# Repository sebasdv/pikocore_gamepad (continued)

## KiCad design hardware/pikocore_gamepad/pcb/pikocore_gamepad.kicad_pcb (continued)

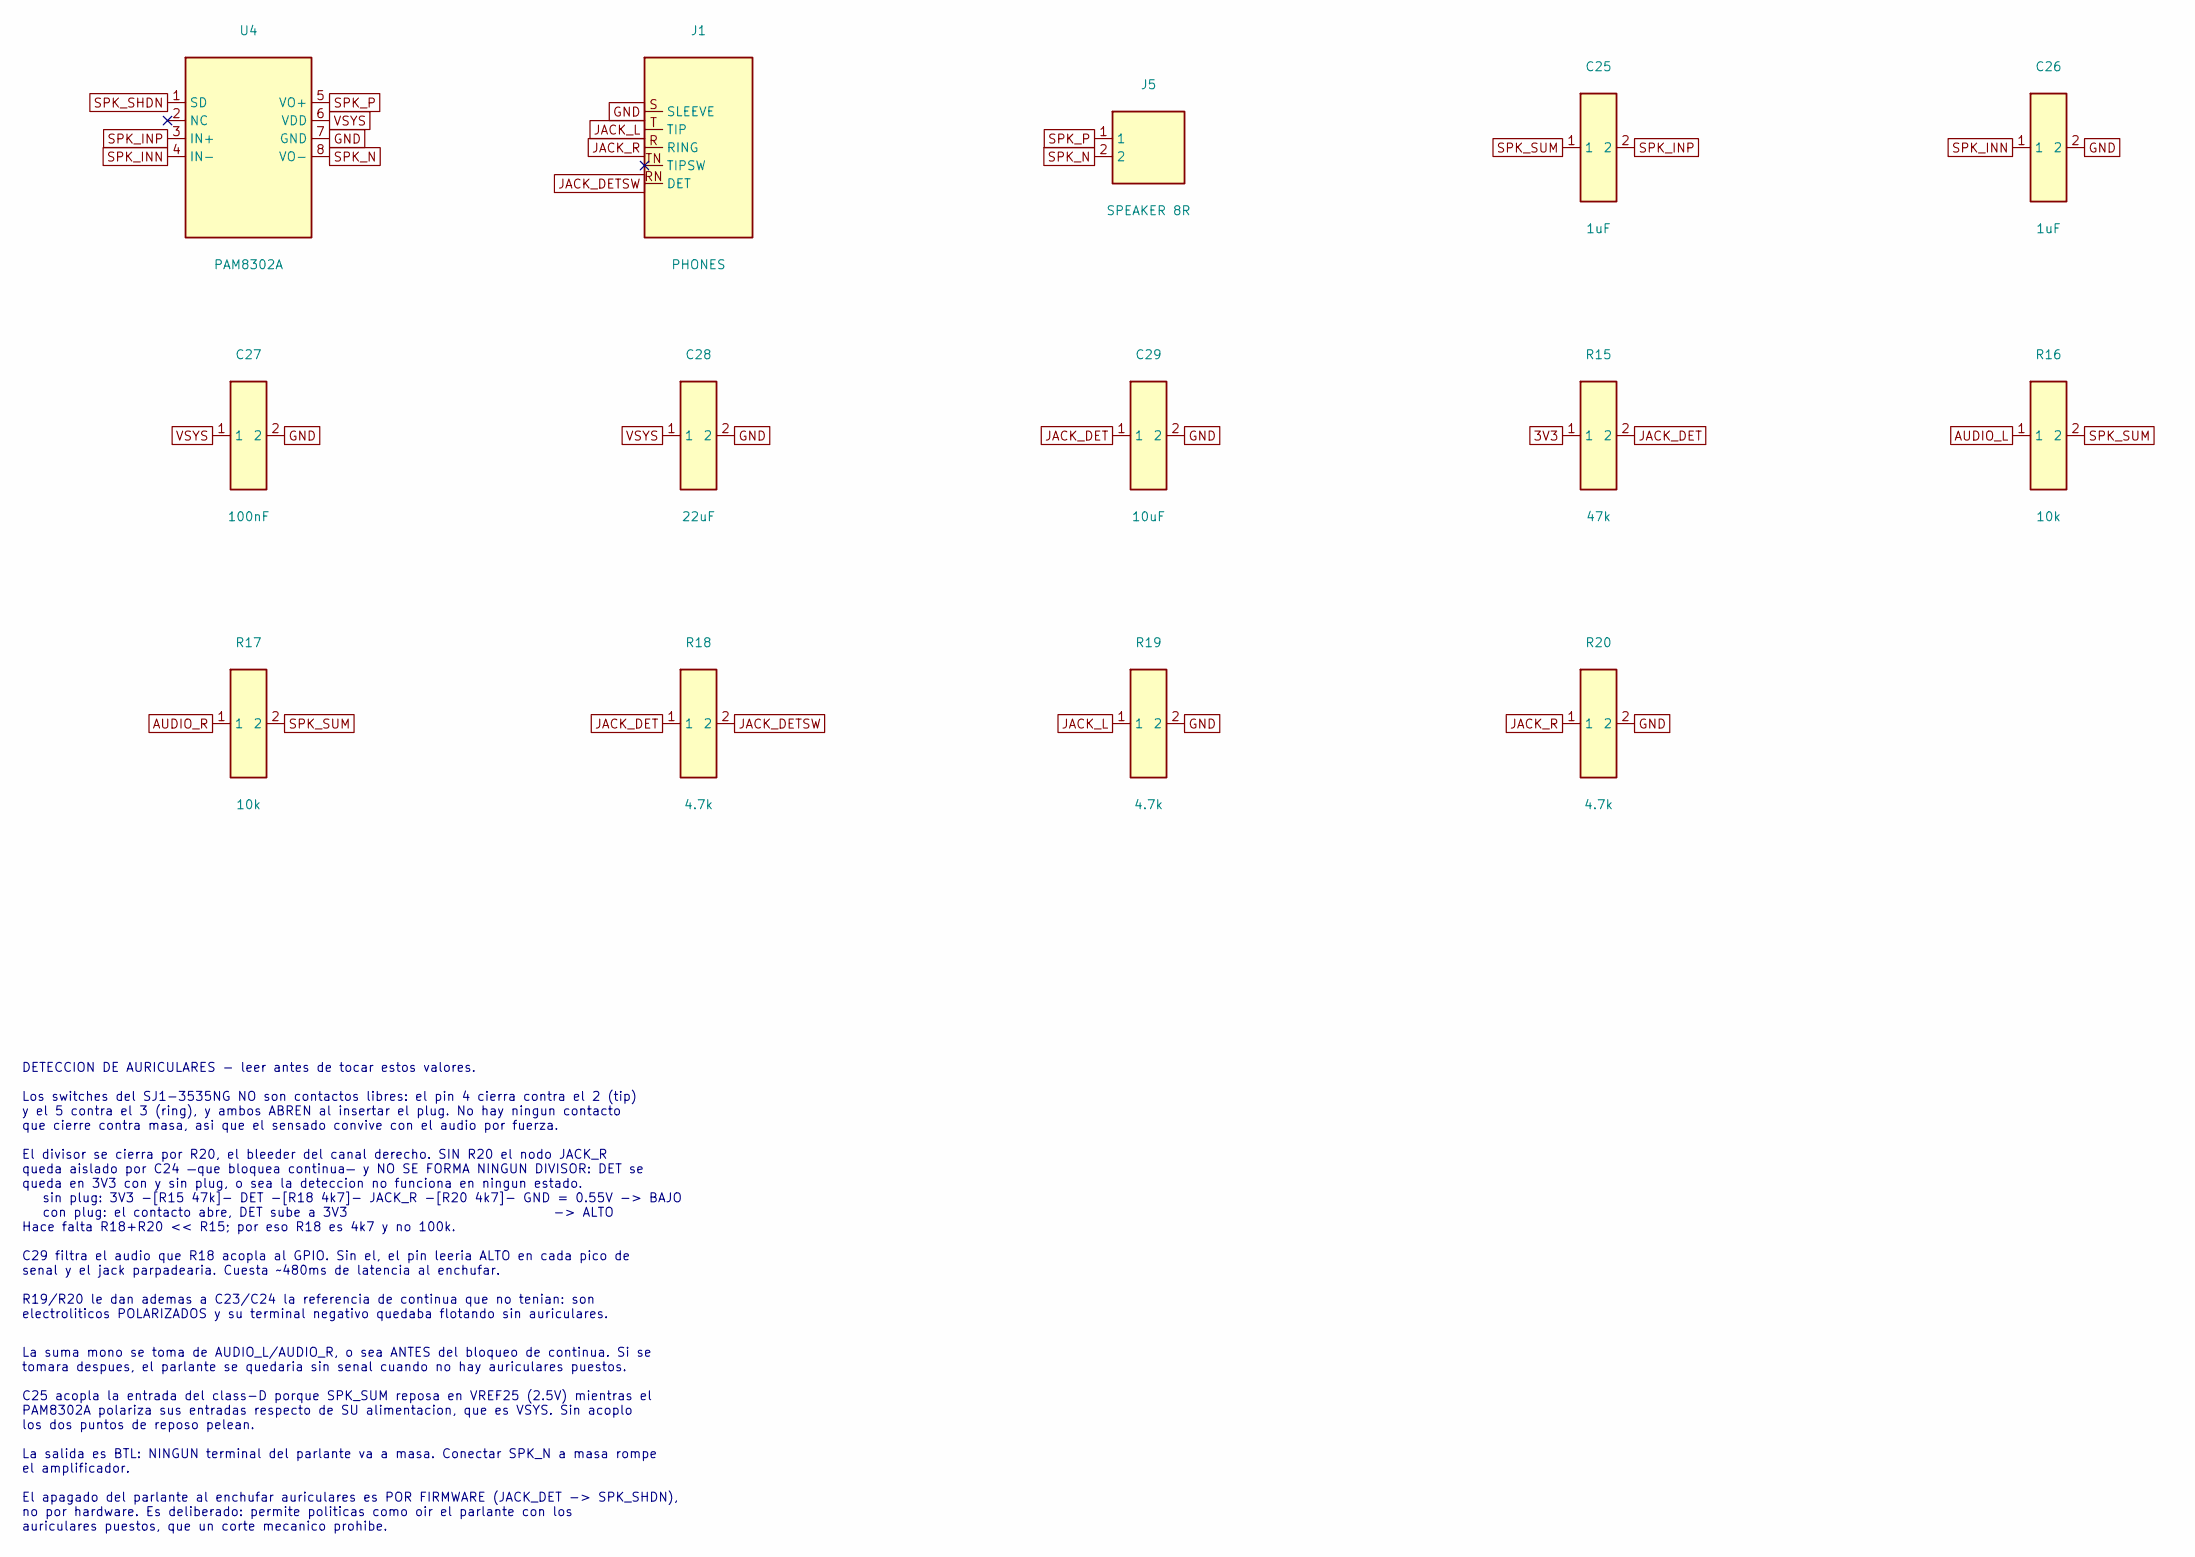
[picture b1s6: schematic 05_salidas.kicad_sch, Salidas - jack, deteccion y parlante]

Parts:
C25, C26: 1uF; C_0603_1608Metric; LCSC C15849
C27: 100nF; C_0603_1608Metric; LCSC C14663
C28: 22uF; C_0805_2012Metric; LCSC C45783
C29: 10uF; C_0603_1608Metric; LCSC C19702
J1: PHONES; Jack_3.5mm_CUI_SJ1-3535NG_Horizontal
J5: SPEAKER 8R; JST_PH_B2B-PH-K_1x02_P2.00mm_Vertical
R15: 47k; R_0603_1608Metric; LCSC C25819
R16, R17: 10k; R_0603_1608Metric; LCSC C25804
R18, R19, R20: 4.7k; R_0603_1608Metric; LCSC C23162
U4: PAM8302A; MSOP-8_L3.0-W3.0-P0.65-LS5.0-BL; LCSC C113367

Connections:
3V3: R15.1; also elsewhere on the board
AUDIO_L: R16.1; also elsewhere on the board
AUDIO_R: R17.1; also elsewhere on the board
GND: C26.2, C27.2, C28.2, C29.2, J1.S (SLEEVE), R19.2, R20.2, U4.7 (GND); also elsewhere on the board
JACK_DET: C29.1, R15.2, R18.1; also elsewhere on the board
JACK_DETSW: J1.RN (DET), R18.2
JACK_L: J1.T (TIP), R19.1; also elsewhere on the board
JACK_R: J1.R (RING), R20.1; also elsewhere on the board
SPK_INN: C26.1, U4.4 (IN-)
SPK_INP: C25.2, U4.3 (IN+)
SPK_N: J5.2, U4.8 (VO-)
SPK_P: J5.1, U4.5 (VO+)
SPK_SHDN: U4.1 (SD); also elsewhere on the board
SPK_SUM: C25.1, R16.2, R17.2
VSYS: C27.1, C28.1, U4.6 (VDD); also elsewhere on the board

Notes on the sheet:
DETECCION DE AURICULARES - leer antes de tocar estos valores. Los switches del SJ1-3535NG NO son contactos libres: el pin 4 cierra contra el 2 (tip) y el 5 contra el 3 (ring), y ambos ABREN al insertar el plug. No hay ningun contacto que cierre contra masa, asi que el sensado convive con el audio p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
La suma mono se toma de AUDIO_L/AUDIO_R, o sea ANTES del bloqueo de continua. Si se tomara despues, el parlante se quedaria sin senal cuando no hay auriculares puestos. C25 acopla la entrada del class-D porque SPK_SUM reposa en VREF25 (2.5V) mientras el PAM8302A polariza sus entradas respecto de SU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

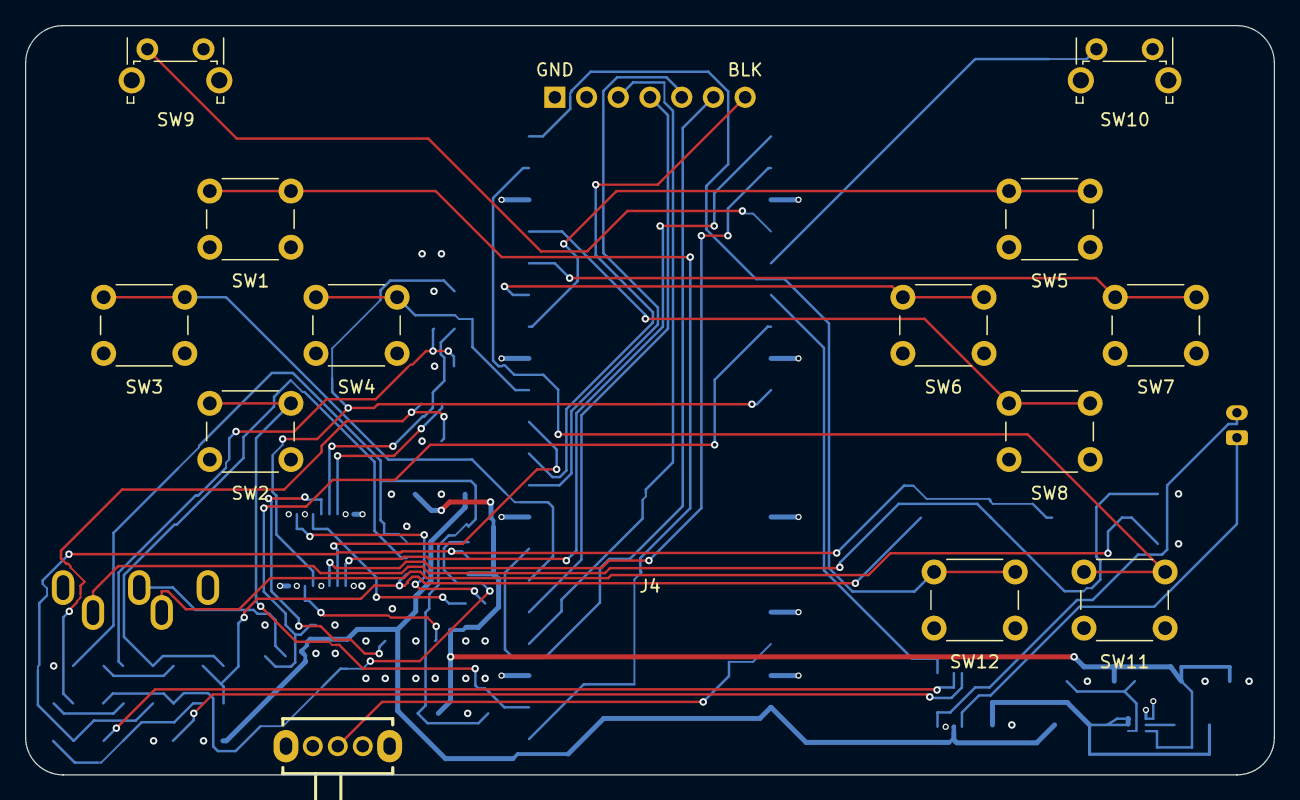
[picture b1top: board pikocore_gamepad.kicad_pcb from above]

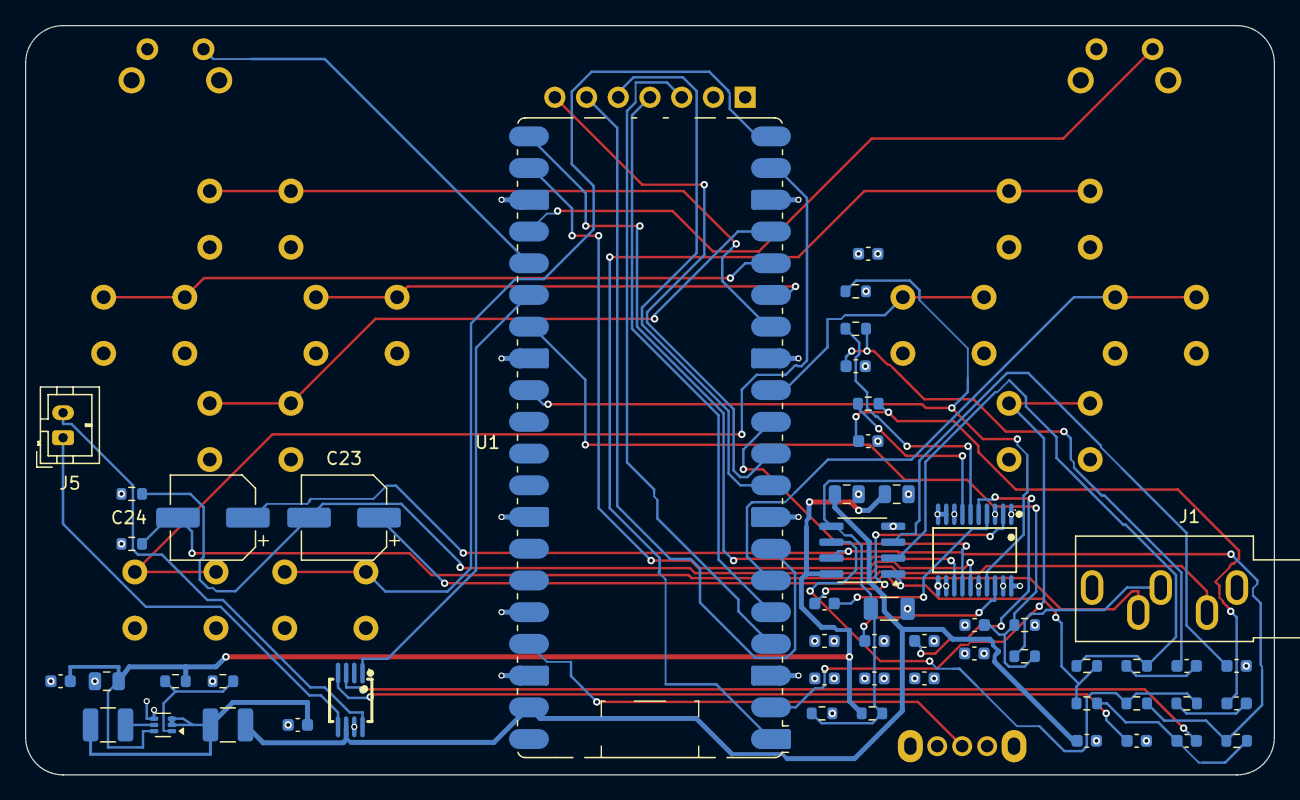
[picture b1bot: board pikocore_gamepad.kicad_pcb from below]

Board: 4 copper layers, 100.0 x 60.0 mm, 66 parts (52 on the bottom side), 54 nets.

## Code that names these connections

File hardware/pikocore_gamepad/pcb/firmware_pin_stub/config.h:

#pragma once

// ============================================================
// pikocore_gamepad — firmware pin-map STUB, not a real board config.
//
// Exists only so checks/check_pinmap.py (gate G-4) has something to diff
// pinmap.py against. NOT included by any CMake target. When the real
// firmware repin happens (separate plan, per the hardware design spec's
// "out of scope" section), replace every reference to this file in
// check_pinmap.py with the real board config header and delete this stub.
//
// Source of truth: hardware/pikocore_gamepad/pcb/pinmap.py
// ============================================================

#define PIN_DPAD_UP      0
#define PIN_DPAD_DOWN    1
#define PIN_LCD_SCK      2
#define PIN_LCD_MOSI     3
#define PIN_DPAD_LEFT    4
#define PIN_LCD_DC       5
#define PIN_LCD_RES      6
#define PIN_LCD_BLK      7
#define PIN_I2S_DIN      8
#define PIN_DPAD_RIGHT   9
#define PIN_BTN_X        10
#define PIN_BTN_Y        11
#define PIN_BTN_A        12
#define PIN_BTN_B        13
#define PIN_BTN_START    14
#define PIN_BTN_SELECT   15
#define PIN_I2S_BCK      16
#define PIN_I2S_LRCK     17
#define PIN_BTN_L        18
#define PIN_BTN_R        19
#define PIN_SPK_SHDN     20
#define PIN_JACK_DET     21
#define PIN_DAC_XSMT     22
#define PIN_LCD_TE       26
